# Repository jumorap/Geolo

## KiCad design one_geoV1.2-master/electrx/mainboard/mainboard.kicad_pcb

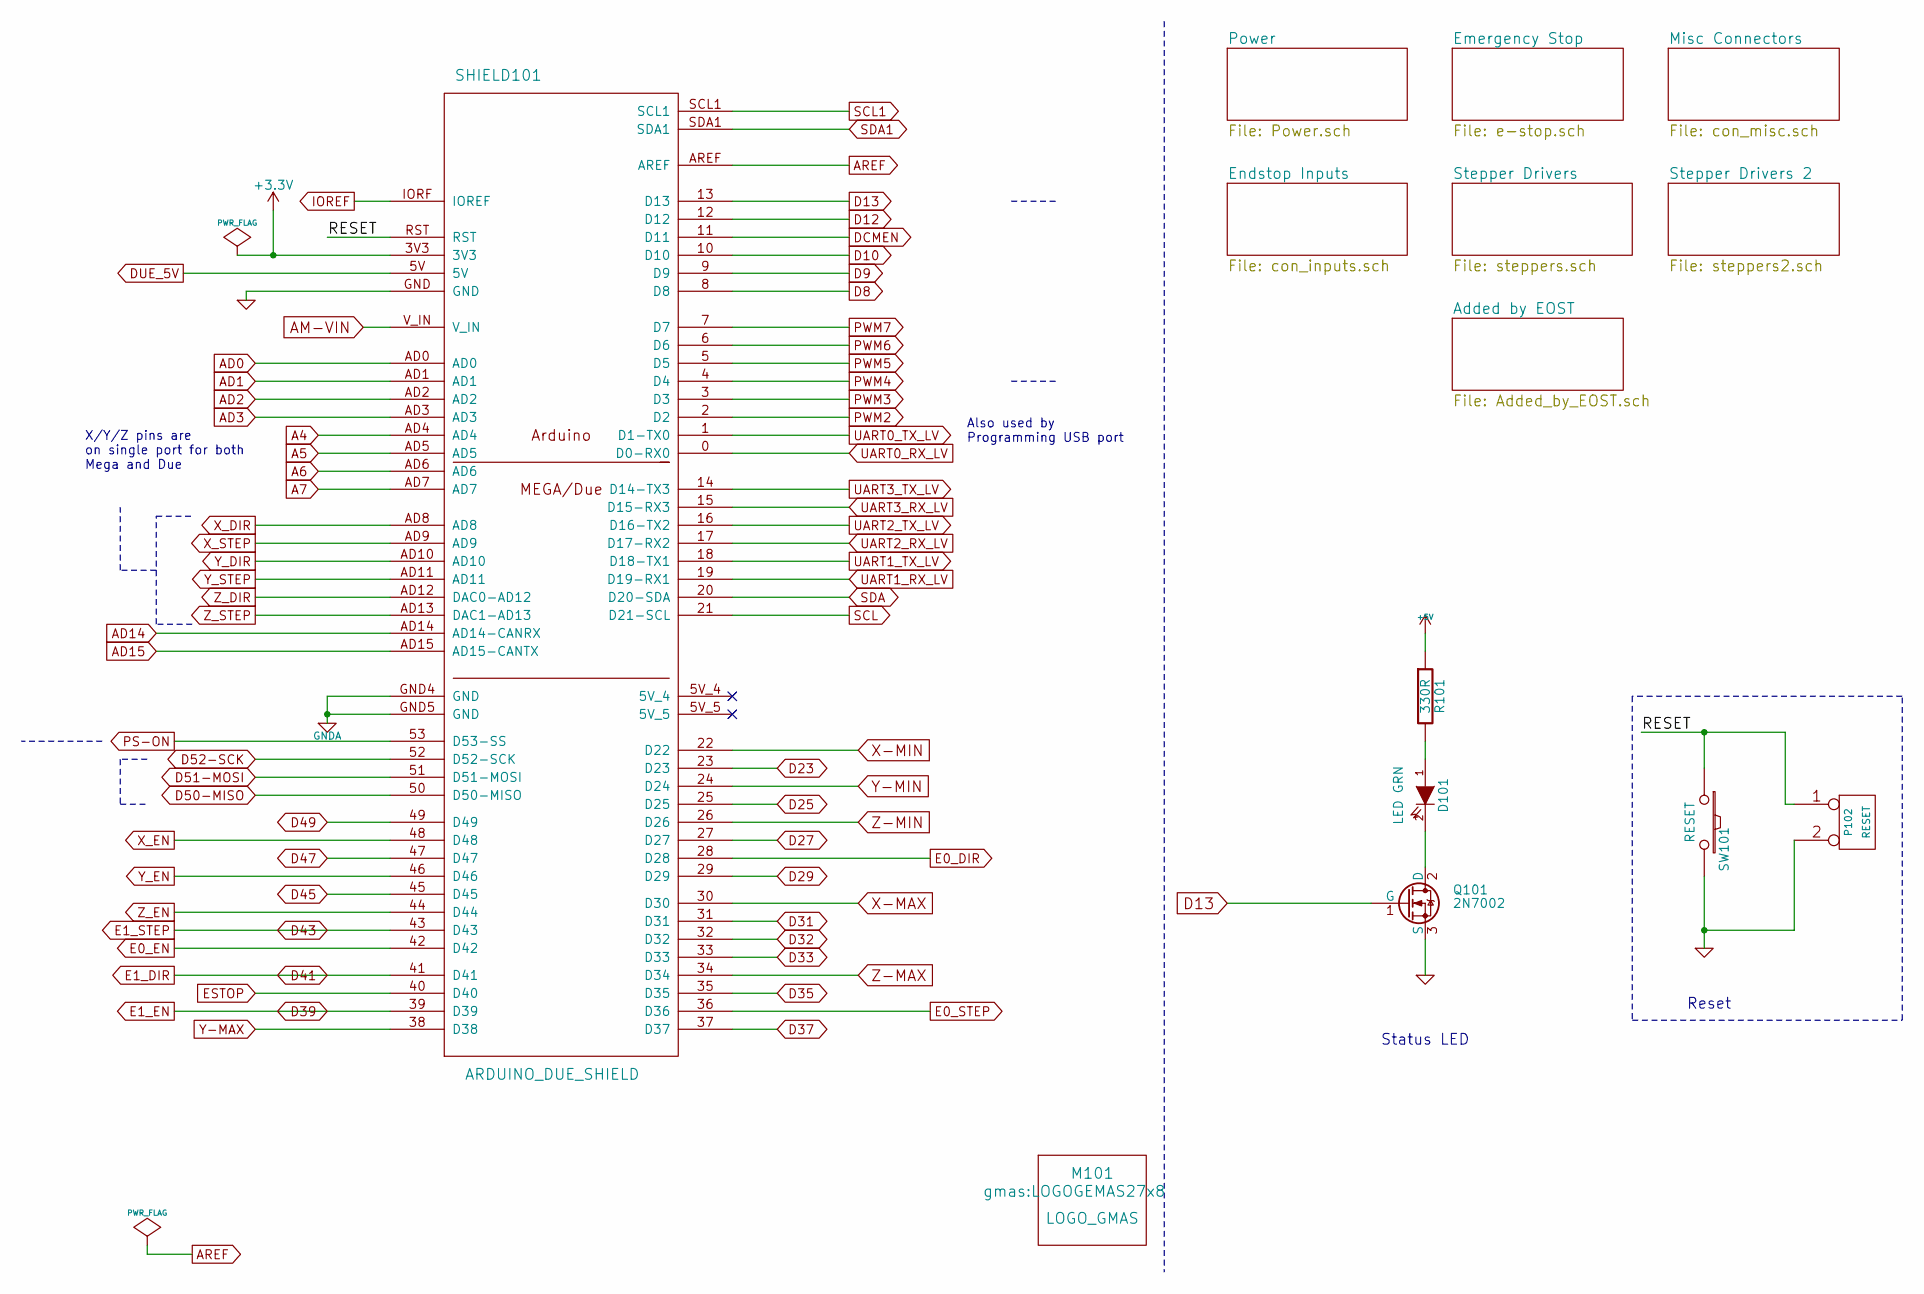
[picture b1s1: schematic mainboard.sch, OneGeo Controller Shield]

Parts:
D101: LED GRN; LED-0805_GREEN
M101: LOGO_GMAS; LOGOGEMAS27x8
P102: RESET; pin_strip_2
Q101: 2N7002; sot23
R101: 330R; SM0805_Opendous
SHIELD101: ARDUINO_DUE_SHIELD; ARDUINO_MEGA_DUE_SHIELD_FOOTPRINT_RMC
SW101: RESET; SW_6x6_MULTI

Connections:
+3V3: SHIELD101.3V3
/RESET: P102.1, SHIELD101.RST, SW101.1
A4: SHIELD101.AD4; also elsewhere on the board
A5: SHIELD101.AD5; also elsewhere on the board
A6: SHIELD101.AD6; also elsewhere on the board
A7: SHIELD101.AD7; also elsewhere on the board
AD0: SHIELD101.AD0
AD1: SHIELD101.AD1
AD2: SHIELD101.AD2
AD3: SHIELD101.AD3
AD14: SHIELD101.AD14 (AD14-CANRX); also elsewhere on the board
AD15: SHIELD101.AD15 (AD15-CANTX); also elsewhere on the board
AM-VIN: SHIELD101.V_IN
AREF: SHIELD101.AREF
D8: SHIELD101.8 (D8)
D9: SHIELD101.9 (D9)
D10: SHIELD101.10 (D10)
D12: SHIELD101.12 (D12)
D13: Q101.1 (G), SHIELD101.13 (D13)
D23: SHIELD101.23 (D23); also elsewhere on the board
D25: SHIELD101.25 (D25); also elsewhere on the board
D27: SHIELD101.27 (D27); also elsewhere on the board
D29: SHIELD101.29 (D29); also elsewhere on the board
D31: SHIELD101.31 (D31); also elsewhere on the board
D32: SHIELD101.32 (D32); also elsewhere on the board
D33: SHIELD101.33 (D33); also elsewhere on the board
D35: SHIELD101.35 (D35); also elsewhere on the board
D37: SHIELD101.37 (D37); also elsewhere on the board
D39: SHIELD101.39 (D39); also elsewhere on the board
D41: SHIELD101.41 (D41); also elsewhere on the board
D43: SHIELD101.43 (D43); also elsewhere on the board
D45: SHIELD101.45 (D45); also elsewhere on the board
D47: SHIELD101.47 (D47); also elsewhere on the board
D49: SHIELD101.49 (D49); also elsewhere on the board
D50-MISO: SHIELD101.50 (D50-MISO)
D51-MOSI: SHIELD101.51 (D51-MOSI)
D52-SCK: SHIELD101.52 (D52-SCK)
DCMEN: SHIELD101.11 (D11); also elsewhere on the board
DUE_5V: SHIELD101.5V
E0_DIR: SHIELD101.28 (D28); also elsewhere on the board
E0_EN: SHIELD101.42 (D42); also elsewhere on the board
E0_STEP: SHIELD101.36 (D36); also elsewhere on the board
ESTOP: SHIELD101.40 (D40); also elsewhere on the board
FD_5V: R101.1; also elsewhere on the board
GNDA: SHIELD101.GND4 (GND), SHIELD101.GND5 (GND)
IOREF: SHIELD101.IORF (IOREF)
MOT_GND: P102.2 (PM), Q101.3 (S), SHIELD101.GND, SW101.2; also elsewhere on the board
unnamed: D101.1 (A), R101.2
unnamed: D101.2 (K), Q101.2 (D)
PS-ON: SHIELD101.53 (D53-SS); also elsewhere on the board
PWM2: SHIELD101.2 (D2); also elsewhere on the board
PWM3: SHIELD101.3 (D3); also elsewhere on the board
PWM4: SHIELD101.4 (D4); also elsewhere on the board
PWM5: SHIELD101.5 (D5); also elsewhere on the board
PWM6: SHIELD101.6 (D6); also elsewhere on the board
PWM7: SHIELD101.7 (D7); also elsewhere on the board
SCL: SHIELD101.21 (D21-SCL); also elsewhere on the board
SCL1: SHIELD101.SCL1; also elsewhere on the board
SDA: SHIELD101.20 (D20-SDA); also elsewhere on the board
SDA1: SHIELD101.SDA1; also elsewhere on the board
UART0_RX_LV: SHIELD101.0 (D0-RX0); also elsewhere on the board
UART0_TX_LV: SHIELD101.1 (D1-TX0); also elsewhere on the board
UART1_RX_LV: SHIELD101.19 (D19-RX1); also elsewhere on the board
UART1_TX_LV: SHIELD101.18 (D18-TX1); also elsewhere on the board
UART2_RX_LV: SHIELD101.17 (D17-RX2); also elsewhere on the board
UART2_TX_LV: SHIELD101.16 (D16-TX2); also elsewhere on the board
UART3_RX_LV: SHIELD101.15 (D15-RX3); also elsewhere on the board
UART3_TX_LV: SHIELD101.14 (D14-TX3); also elsewhere on the board
X-MAX: SHIELD101.30 (D30); also elsewhere on the board
X-MIN: SHIELD101.22 (D22); also elsewhere on the board
X_DIR: SHIELD101.AD8; also elsewhere on the board
X_EN: SHIELD101.48 (D48); also elsewhere on the board
X_STEP: SHIELD101.AD9; also elsewhere on the board
Y-MAX: SHIELD101.38 (D38); also elsewhere on the board
Y-MIN: SHIELD101.24 (D24); also elsewhere on the board
Y_DIR: SHIELD101.AD10; also elsewhere on the board
Y_EN: SHIELD101.46 (D46); also elsewhere on the board
Y_STEP: SHIELD101.AD11; also elsewhere on the board
Z-MAX: SHIELD101.34 (D34); also elsewhere on the board
Z-MIN: SHIELD101.26 (D26); also elsewhere on the board
Z_DIR: SHIELD101.AD12 (DAC0-AD12); also elsewhere on the board
Z_EN: SHIELD101.44 (D44); also elsewhere on the board
Z_STEP: SHIELD101.AD13 (DAC1-AD13); also elsewhere on the board

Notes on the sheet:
Also used by Programming USB port
X/Y/Z pins are on single port for both Mega and Due
Reset
Status LED

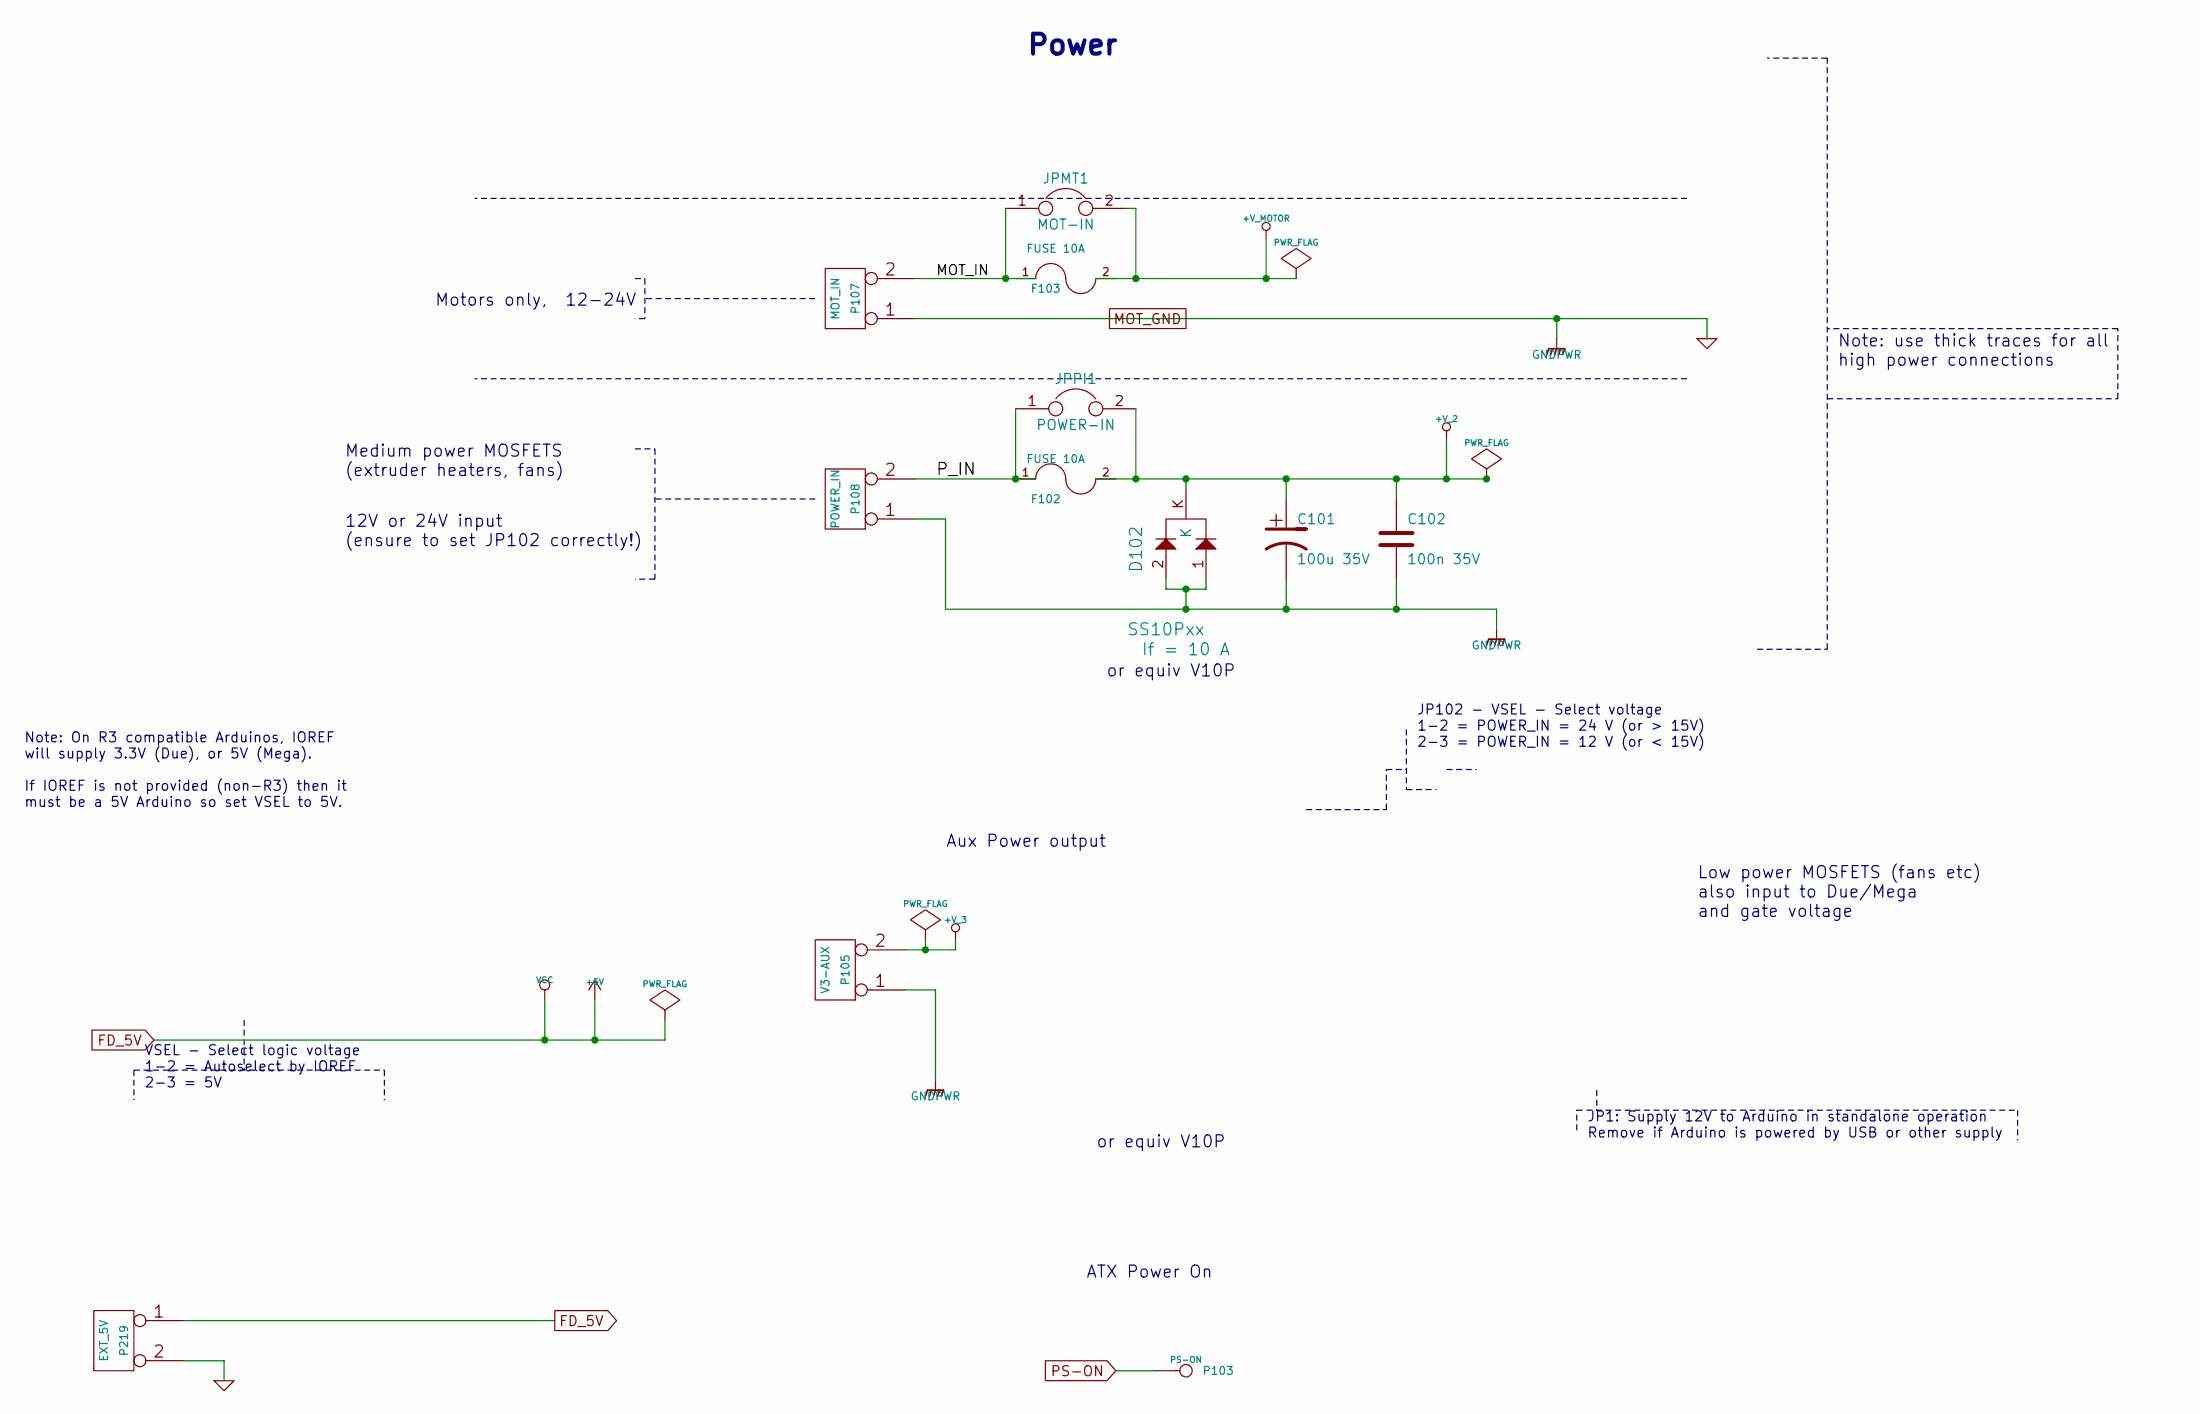
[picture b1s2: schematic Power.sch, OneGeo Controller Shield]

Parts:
C101: 100u 35V; c_elec_6.3x7.7
C102: 100n 35V; SM0805_Opendous
D102: SS10Pxx; TO277A_RMC
F102, F103: FUSE 10A; Fuse_Holder_bayoneta
JPMT1: MOT-IN; pin_socket_2
JPPI1: POWER-IN; pin_socket_2
P103: PS-ON; pin_strip_1
P105: V3-AUX; mors_2p
P107: MOT_IN; mors_2p
P108: POWER_IN; mors_2p
P219: EXT_5V; CONN_KK_2.54_2W

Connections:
+V_2: C101.1, C102.1, D102.K, F102.2, JPPI1.2; also elsewhere on the board
+V_3: P105.2 (PM); also elsewhere on the board
+V_MOTOR: F103.2, JPMT1.2; also elsewhere on the board
/Power/MOT_IN: F103.1, JPMT1.1, P107.2 (PM)
/Power/P_IN: F102.1, JPPI1.1, P108.2 (PM)
FD_5V: P219.1; also elsewhere on the board
MOT_GND: C101.2, C102.2, D102.1, D102.2, P105.1, P107.1, P108.1, P219.2 (PM); also elsewhere on the board
PS-ON: P103.1; also elsewhere on the board

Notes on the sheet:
JP102 - VSEL - Select voltage 1-2 = POWER_IN = 24 V (or > 15V) 2-3 = POWER_IN = 12 V (or < 15V)
Low power MOSFETS (fans etc) also input to Due/Mega and gate voltage
Aux Power output
VSEL - Select logic voltage 1-2 = Autoselect by IOREF 2-3 = 5V
Note: On R3 compatible Arduinos, IOREF will supply 3.3V (Due), or 5V (Mega). If IOREF is not provided (non-R3) then it must be a 5V Arduino so set VSEL to 5V.
Medium power MOSFETS (extruder heaters, fans)
Motors only, 12-24V
Power
JP1: Supply 12V to Arduino in standalone operation Remove if Arduino is powered by USB or other supply
Note: use thick traces for all high power connections
12V or 24V input (ensure to set JP102 correctly!)
ATX Power On
or equiv V10P

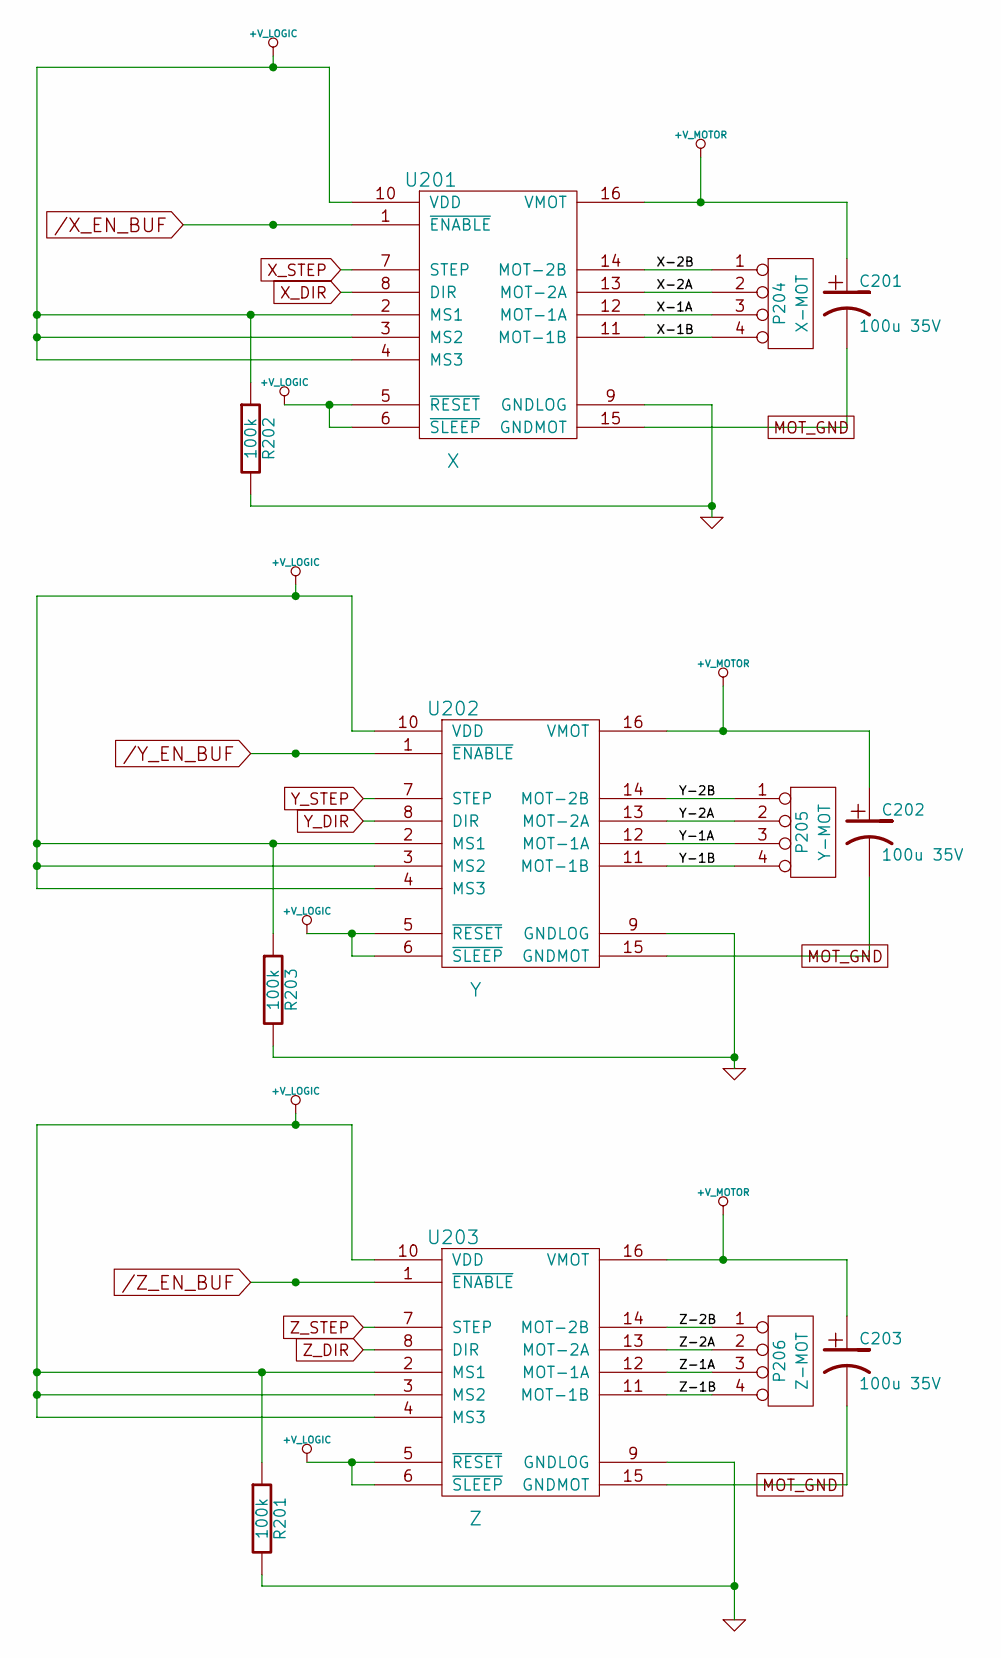
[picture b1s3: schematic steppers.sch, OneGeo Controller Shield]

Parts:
C201, C202, C203: 100u 35V; c_elec_6.3x7.7
P204: X-MOT; CONN_KK_2.54_4W
P205: Y-MOT; CONN_KK_2.54_4W
P206: Z-MOT; CONN_KK_2.54_4W
R201, R202, R203: 100k; SM0805_Opendous
U201: X; POLOLU
U202: Y; POLOLU
U203: Z; POLOLU

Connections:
+V_LOGIC: R201.1, R202.1, R203.1, U201.2 (MS1), U201.3 (MS2), U201.4 (MS3), U201.5 (~RESET), U201.6 (~SLEEP), U201.10 (VDD), U202.2 (MS1), U202.3 (MS2), U202.4 (MS3), U202.5 (~RESET), U202.6 (~SLEEP), U202.10 (VDD), U203.2 (MS1), U203.3 (MS2), U203.4 (MS3), U203.5 (~RESET), U203.6 (~SLEEP), U203.10 (VDD); also elsewhere on the board
+V_MOTOR: C201.1, C202.1, C203.1, U201.16 (VMOT), U202.16 (VMOT), U203.16 (VMOT); also elsewhere on the board
/Stepper Drivers/X-1A: P204.3, U201.12 (MOT-1A)
/Stepper Drivers/X-1B: P204.4, U201.11 (MOT-1B)
/Stepper Drivers/X-2A: P204.2, U201.13 (MOT-2A)
/Stepper Drivers/X-2B: P204.1, U201.14 (MOT-2B)
/Stepper Drivers/Y-1A: P205.3, U202.12 (MOT-1A)
/Stepper Drivers/Y-1B: P205.4, U202.11 (MOT-1B)
/Stepper Drivers/Y-2A: P205.2, U202.13 (MOT-2A)
/Stepper Drivers/Y-2B: P205.1, U202.14 (MOT-2B)
/Stepper Drivers/Z-1A: P206.3, U203.12 (MOT-1A)
/Stepper Drivers/Z-1B: P206.4, U203.11 (MOT-1B)
/Stepper Drivers/Z-2A: P206.2, U203.13 (MOT-2A)
/Stepper Drivers/Z-2B: P206.1, U203.14 (MOT-2B)
/X_EN_BUF: U201.1 (~ENABLE); also elsewhere on the board
/Y_EN_BUF: U202.1 (~ENABLE); also elsewhere on the board
/Z_EN_BUF: U203.1 (~ENABLE); also elsewhere on the board
MOT_GND: C201.2, C202.2, C203.2, R201.2, R202.2, R203.2, U201.9 (GNDLOG), U201.15 (GNDMOT), U202.9 (GNDLOG), U202.15 (GNDMOT), U203.9 (GNDLOG), U203.15 (GNDMOT); also elsewhere on the board
X_DIR: U201.8 (DIR); also elsewhere on the board
X_STEP: U201.7 (STEP); also elsewhere on the board
Y_DIR: U202.8 (DIR); also elsewhere on the board
Y_STEP: U202.7 (STEP); also elsewhere on the board
Z_DIR: U203.8 (DIR); also elsewhere on the board
Z_STEP: U203.7 (STEP); also elsewhere on the board

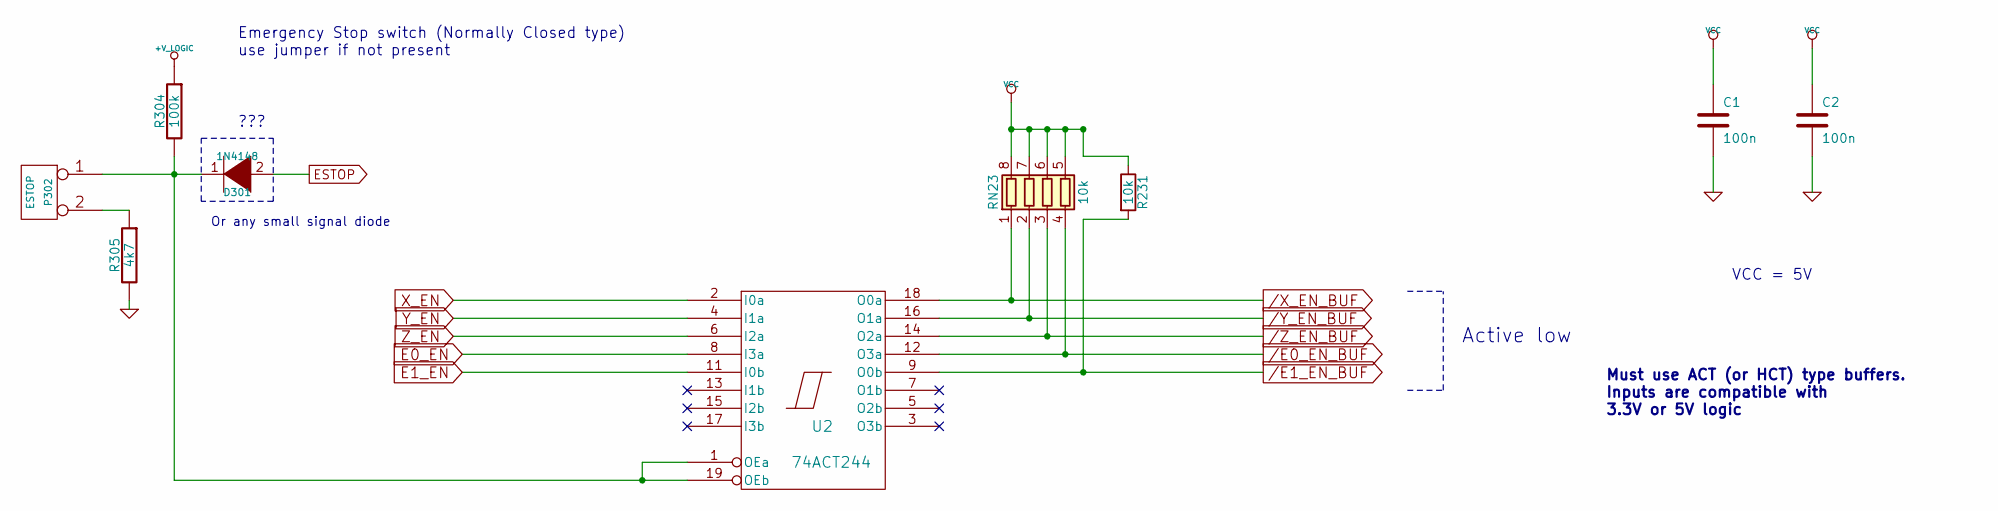
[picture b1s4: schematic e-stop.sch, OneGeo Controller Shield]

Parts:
C1, C2: 100n; SM0805_Opendous
D301: 1N4148; SOD323
P302: ESTOP; CONN_KK_2.54_2W
R231: 10k; SM0805_Opendous
R304: 100k; SM0805_Opendous
R305: 4k7; SM0805_Opendous
RN23: 10k; R_Array_Concave_4x0603
U2: 74ACT244; soic-20

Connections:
+V_LOGIC: R304.1; also elsewhere on the board
/E0_EN_BUF: RN23.4 (R4.1), U2.12 (O3a); also elsewhere on the board
/E1_EN_BUF: R231.2, U2.9 (O0b); also elsewhere on the board
/X_EN_BUF: RN23.1 (R1.1), U2.18 (O0a); also elsewhere on the board
/Y_EN_BUF: RN23.2 (R2.1), U2.16 (O1a); also elsewhere on the board
/Z_EN_BUF: RN23.3 (R3.1), U2.14 (O2a); also elsewhere on the board
D39: U2.11 (I0b); also elsewhere on the board
E0_EN: U2.8 (I3a); also elsewhere on the board
ESTOP: D301.2 (A); also elsewhere on the board
FD_5V: C1.1, C2.1, R231.1, RN23.5 (R4.2), RN23.6 (R3.2), RN23.7 (R2.2), RN23.8 (R1.2), U2.20 (VCC); also elsewhere on the board
MOT_GND: C1.2, C2.2, R305.2, U2.10 (GND); also elsewhere on the board
unnamed: D301.1 (K), P302.1, R304.2, U2.1 (OEa), U2.19 (OEb)
unnamed: P302.2 (PM), R305.1
X_EN: U2.2 (I0a); also elsewhere on the board
Y_EN: U2.4 (I1a); also elsewhere on the board
Z_EN: U2.6 (I2a); also elsewhere on the board

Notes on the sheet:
Emergency Stop switch (Normally Closed type) use jumper if not present
Or any small signal diode
Active low
VCC = 5V
Must use ACT (or HCT) type buffers. Inputs are compatible with 3.3V or 5V logic
???

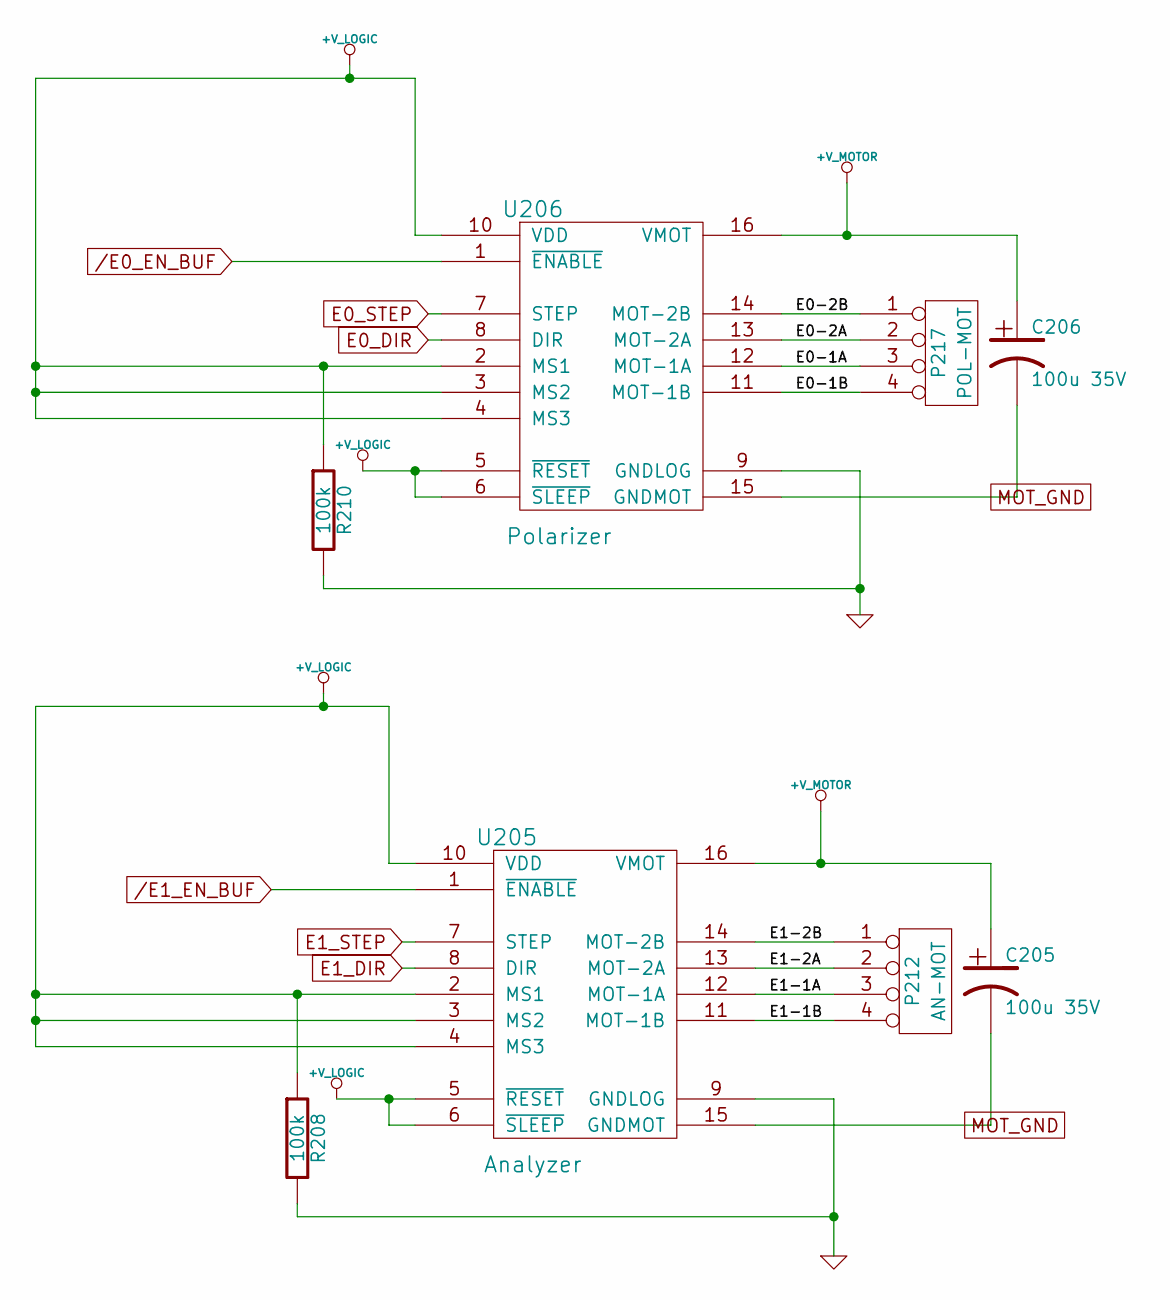
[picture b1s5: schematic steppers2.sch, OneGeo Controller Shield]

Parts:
C205, C206: 100u 35V; c_elec_6.3x7.7
P212: AN-MOT; CONN_KK_2.54_4W
P217: POL-MOT; CONN_KK_2.54_4W
R208, R210: 100k; SM0805_Opendous
U205: Analyzer; POLOLU
U206: Polarizer; POLOLU

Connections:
+V_LOGIC: R208.1, R210.1, U205.2 (MS1), U205.3 (MS2), U205.4 (MS3), U205.5 (~RESET), U205.6 (~SLEEP), U205.10 (VDD), U206.2 (MS1), U206.3 (MS2), U206.4 (MS3), U206.5 (~RESET), U206.6 (~SLEEP), U206.10 (VDD); also elsewhere on the board
+V_MOTOR: C205.1, C206.1, U205.16 (VMOT), U206.16 (VMOT); also elsewhere on the board
/E0_EN_BUF: U206.1 (~ENABLE); also elsewhere on the board
/E1_EN_BUF: U205.1 (~ENABLE); also elsewhere on the board
/Stepper Drivers 2/E0-1A: P217.3, U206.12 (MOT-1A)
/Stepper Drivers 2/E0-1B: P217.4, U206.11 (MOT-1B)
/Stepper Drivers 2/E0-2A: P217.2, U206.13 (MOT-2A)
/Stepper Drivers 2/E0-2B: P217.1, U206.14 (MOT-2B)
/Stepper Drivers 2/E1-1A: P212.3, U205.12 (MOT-1A)
/Stepper Drivers 2/E1-1B: P212.4, U205.11 (MOT-1B)
/Stepper Drivers 2/E1-2A: P212.2, U205.13 (MOT-2A)
/Stepper Drivers 2/E1-2B: P212.1, U205.14 (MOT-2B)
D41: U205.8 (DIR); also elsewhere on the board
D43: U205.7 (STEP); also elsewhere on the board
E0_DIR: U206.8 (DIR); also elsewhere on the board
E0_STEP: U206.7 (STEP); also elsewhere on the board
MOT_GND: C205.2, C206.2, R208.2, R210.2, U205.9 (GNDLOG), U205.15 (GNDMOT), U206.9 (GNDLOG), U206.15 (GNDMOT); also elsewhere on the board

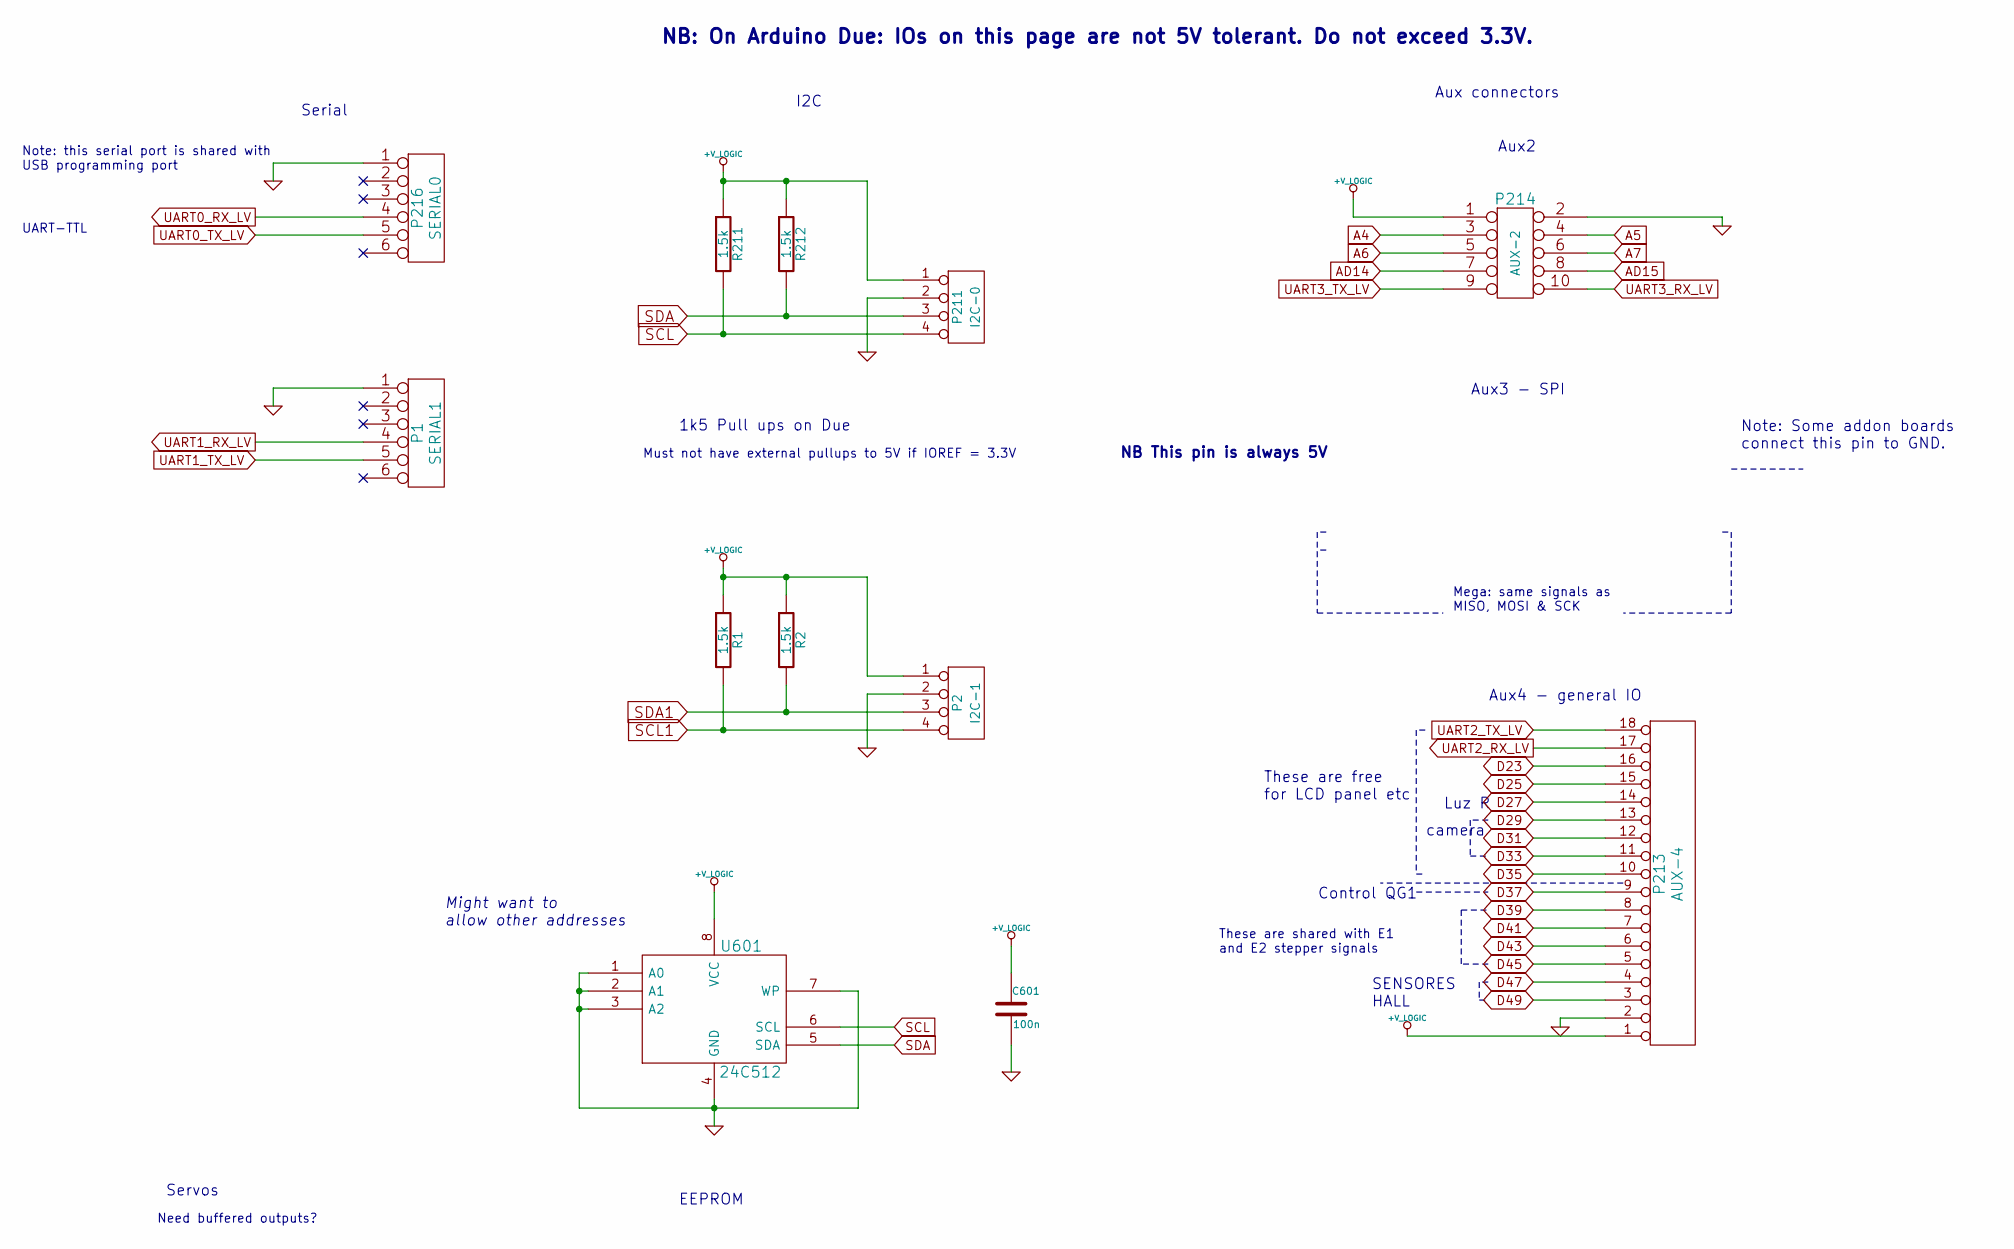
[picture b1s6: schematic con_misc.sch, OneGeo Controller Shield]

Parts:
C601: 100n; SM0805_Opendous
P1: SERIAL1; pin_strip_6
P2: I2C-1; pin_strip_4
P211: I2C-0; pin_strip_4
P213: AUX-4; pin_strip_18
P214: AUX-2; pin_strip_5x2
P216: SERIAL0; pin_strip_6
R1, R2, R211, R212: 1.5k; SM0805_Opendous
U601: 24C512; so-8

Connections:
+V_LOGIC: C601.1, P2.1, P211.1, P213.1, P214.1, R1.1, R2.1, R211.1, R212.1, U601.8 (VCC); also elsewhere on the board
A4: P214.3; also elsewhere on the board
A5: P214.4; also elsewhere on the board
A6: P214.5; also elsewhere on the board
A7: P214.6; also elsewhere on the board
AD14: P214.7; also elsewhere on the board
AD15: P214.8; also elsewhere on the board
D23: P213.16; also elsewhere on the board
D25: P213.15; also elsewhere on the board
D27: P213.14; also elsewhere on the board
D29: P213.13; also elsewhere on the board
D31: P213.12; also elsewhere on the board
D33: P213.11; also elsewhere on the board
D35: P213.10; also elsewhere on the board
D37: P213.9; also elsewhere on the board
D39: P213.8; also elsewhere on the board
D41: P213.7; also elsewhere on the board
D43: P213.6; also elsewhere on the board
D45: P213.5; also elsewhere on the board
D47: P213.4; also elsewhere on the board
D49: P213.3; also elsewhere on the board
MOT_GND: C601.2, P1.1, P2.2, P211.2, P213.2, P214.2, P216.1, U601.1 (A0), U601.2 (A1), U601.3 (A2), U601.4 (GND), U601.7 (WP); also elsewhere on the board
SCL: P211.4, R211.2, U601.6 (SCL); also elsewhere on the board
SCL1: P2.4, R1.2; also elsewhere on the board
SDA: P211.3, R212.2, U601.5 (SDA); also elsewhere on the board
SDA1: P2.3, R2.2; also elsewhere on the board
UART0_RX_LV: P216.4; also elsewhere on the board
UART0_TX_LV: P216.5; also elsewhere on the board
UART1_RX_LV: P1.4; also elsewhere on the board
UART1_TX_LV: P1.5; also elsewhere on the board
UART2_RX_LV: P213.17; also elsewhere on the board
UART2_TX_LV: P213.18; also elsewhere on the board
UART3_RX_LV: P214.10; also elsewhere on the board
UART3_TX_LV: P214.9; also elsewhere on the board

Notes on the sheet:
Serial
UART-TTL
Need buffered outputs?
Must not have external pullups to 5V if IOREF = 3.3V
1k5 Pull ups on Due
Aux4 - general IO
Aux3 - SPI
Aux2
Aux connectors
Servos
I2C
NB: On Arduino Due: IOs on this page are not 5V tolerant. Do not exceed 3.3V.
Note: this serial port is shared with USB programming port
These are shared with E1 and E2 stepper signals
Mega: same signals as MISO, MOSI & SCK
NB This pin is always 5V
These are free for LCD panel etc
Note: Some addon boards connect this pin to GND.
EEPROM
Might want to allow other addresses
SENSORES HALL
Control QG1
camera
Luz R

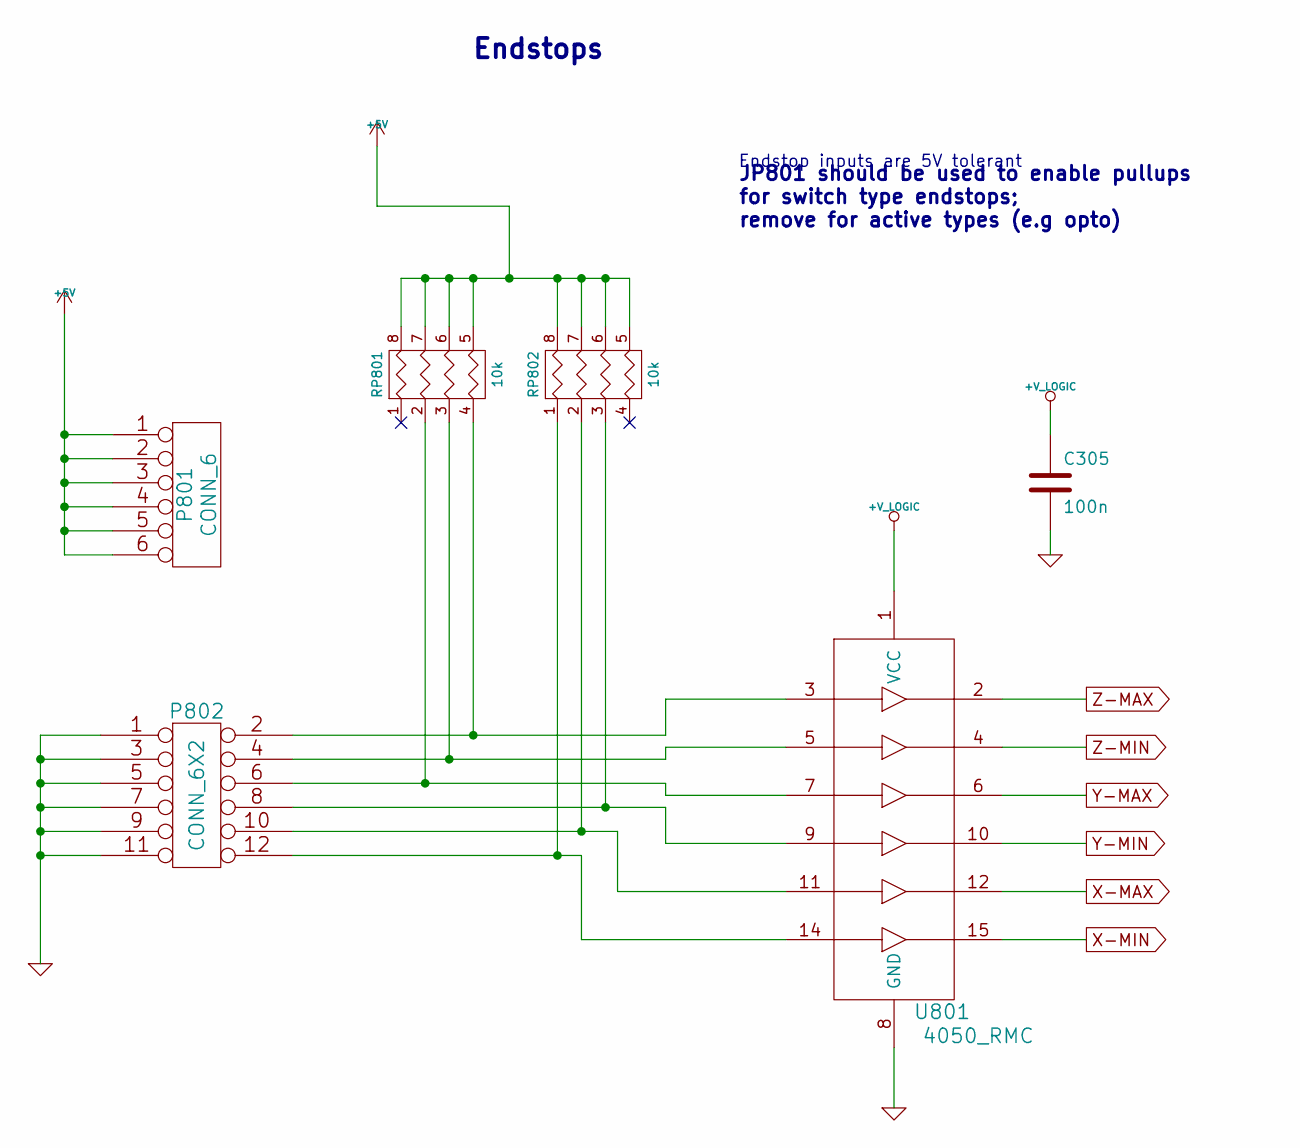
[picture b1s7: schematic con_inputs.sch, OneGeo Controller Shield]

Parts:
C305: 100n; SM0805_Opendous
P801: CONN_6; pin_strip_6
P802: CONN_6X2; pin_strip_6x2
RP801, RP802: 10k; r_cat16-4
U801: 4050_RMC; so-16

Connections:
+V_LOGIC: C305.1, U801.1 (VCC); also elsewhere on the board
FD_5V: P801.1, P801.2, P801.3, P801.4, P801.5, P801.6, RP801.5 (R4), RP801.6 (R3), RP801.7 (R2), RP801.8 (R1), RP802.5 (R4), RP802.6 (R3), RP802.7 (R2), RP802.8 (R1); also elsewhere on the board
MOT_GND: C305.2, P802.1, P802.3, P802.5, P802.7, P802.9, P802.11, U801.8 (GND); also elsewhere on the board
unnamed: P802.2, RP801.4, U801.3
unnamed: P802.4, RP801.3, U801.5
unnamed: P802.6, RP801.2, U801.7
unnamed: P802.8, RP802.3, U801.9
unnamed: P802.10, RP802.2, U801.11
unnamed: P802.12, RP802.1, U801.14
X-MAX: U801.12; also elsewhere on the board
X-MIN: U801.15; also elsewhere on the board
Y-MAX: U801.6; also elsewhere on the board
Y-MIN: U801.10; also elsewhere on the board
Z-MAX: U801.2; also elsewhere on the board
Z-MIN: U801.4; also elsewhere on the board

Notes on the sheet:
Endstop inputs are 5V tolerant
Endstops
JP801 should be used to enable pullups for switch type endstops; remove for active types (e.g opto)

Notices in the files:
one_geoV1.2-master/electrx/RAMPS-FD/Power.sch:
GPL v3
